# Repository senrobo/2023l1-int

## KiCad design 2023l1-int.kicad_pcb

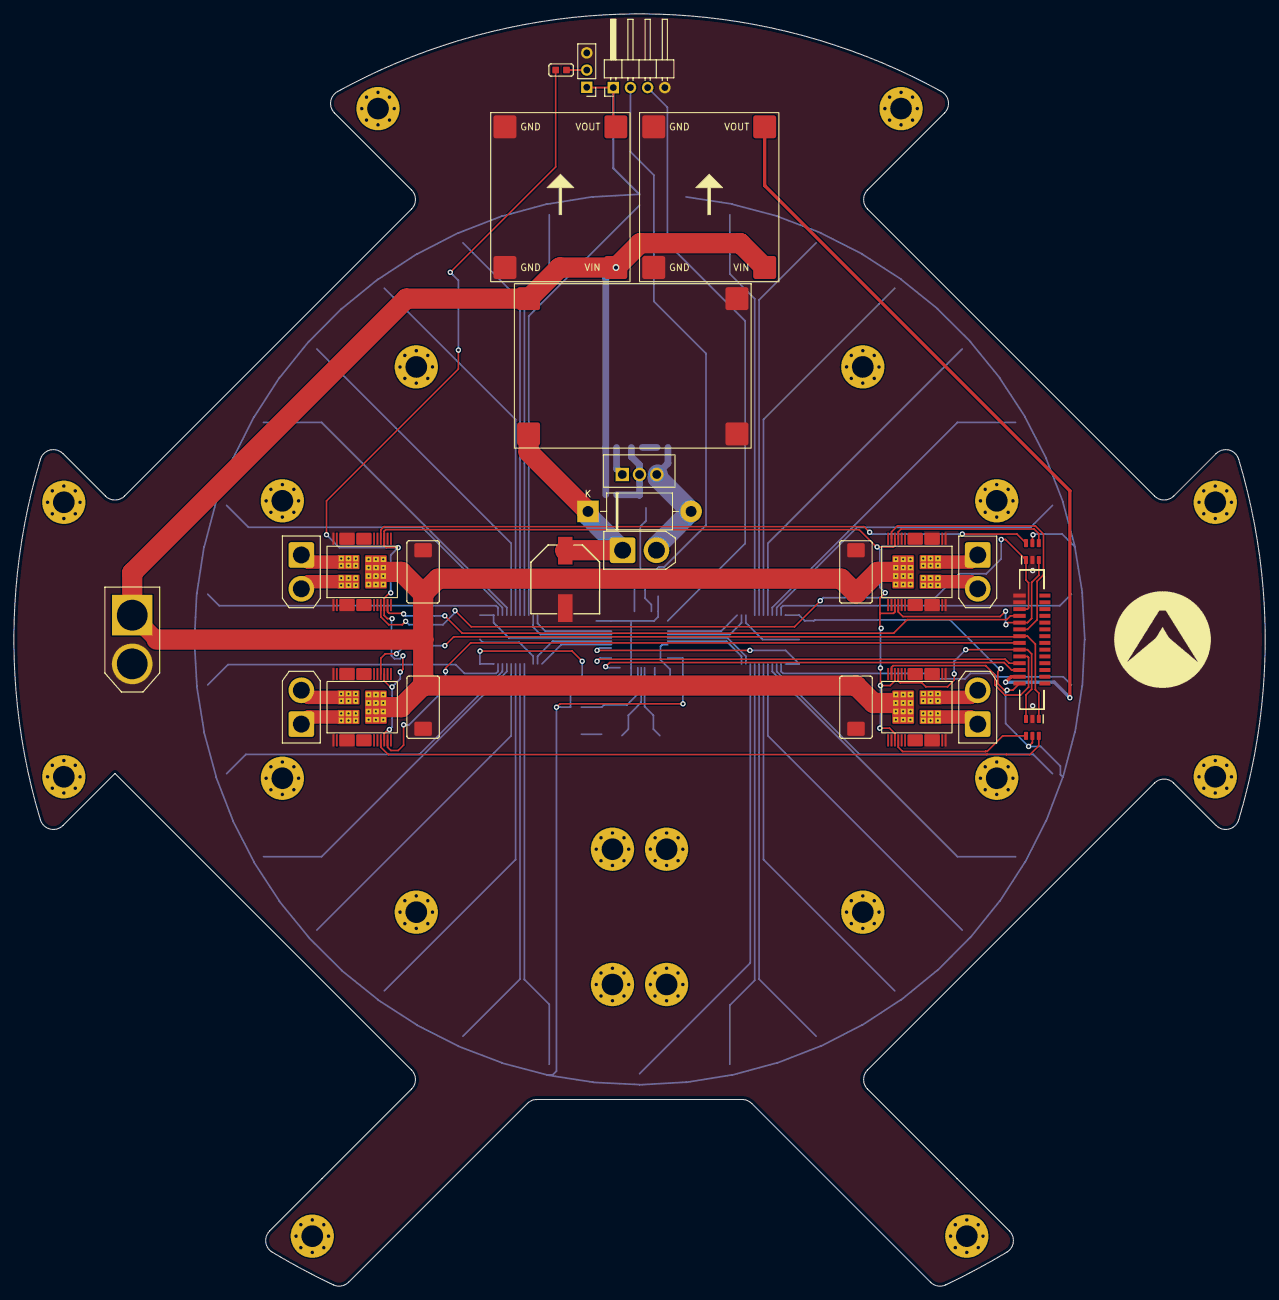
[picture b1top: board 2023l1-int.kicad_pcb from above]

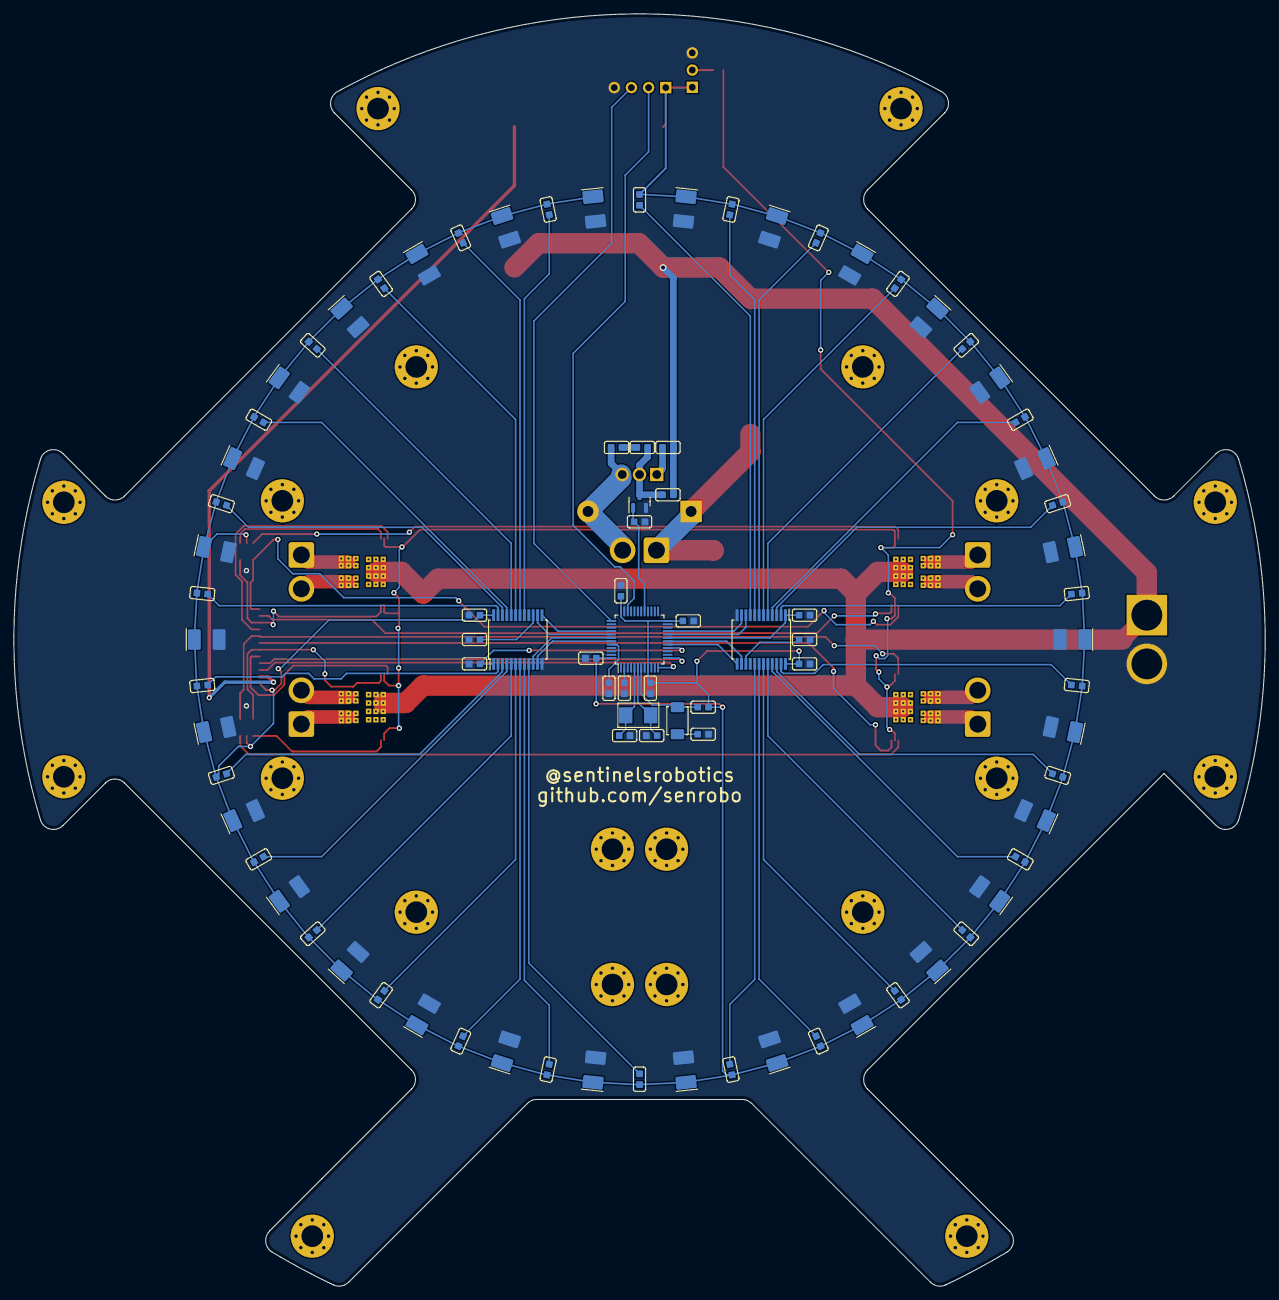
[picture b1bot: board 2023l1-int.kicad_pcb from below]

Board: 2 copper layers, 185.0 x 188.1 mm, 133 parts (87 on the bottom side), 84 nets.

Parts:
Boost1: boost
C4, C5: 22p; cap0603
C6, C12, C13, C14, C15, C20: 0.1u; cap0603
C7: 1500pF; cap0603
C11: 1000u; CAPAE1030X1270N
C16, C17, C18, C19: 220u; EIA-7343-D
D2: 1N5401; D_DO-201AD_P15.24mm_Horizontal
D3: LED; led0603
D5, D6, D7, D8, D9, D10, D11, D12, D13, D14, D15, D16, D17, D18, D19, D20, D21, D22, D23, D24, D25, D26, D27, D28, D29, D30, D31, D32, D33, D34: LED; LED-3528
H1, H2, H3, H4, H5, H6, H7, H8, H9, H10, H11, H12, H13, H14, H15, H16, H17, H18, H19, H20: MountingHole_Pad; MountingHole_3.2mm_M3_Pad_Via
IC1: STM32F103CBTx; LQFP-48_7x7mm_P0.5mm
IC2, IC3: SN74LVC2G04DBVTG4; SOT95P280X145-6N
J1: 52610-1433; 526101433
J2: XT30; AMASS_XT30-F
J3: PGMR; PinHeader_1x04_P2.54mm_Horizontal
J4: FL; AMASS_XT30-F
J5: FR; AMASS_XT30-F
J6: BL; AMASS_XT30-F
J7: BR; AMASS_XT30-F
J8: XT60; AMASS_XT60-M
Q1: STP75NF75; TO255P1040X460X2890-3
Q2: AO3400A; SOT-23
R1, R2, R3, R4, R5, R6, R7, R8, R9, R10, R11, R12, R13, R14, R15, R16, R17, R18, R19, R20, R21, R22, R23, R24, R25, R26, R27, R28, R29, R30: R_Photo; ALS-PT19
R31, R33, R38, R39, R43, R44, R45: 10K; res0603
R35: 20; res0603
R36, R41: 1K; res0603
R37, R42: 3K24; res0603
SW1: STM RST; SW_PUSH_SPST
SW3: M SW; PinHeader_1x03_P2.54mm_Vertical
U1, U3: buck
U2, U4: CD74HC4067SM; SSOP-24_5.3x8.2mm_P0.65mm
U5, U6, U7, U8: VNH5050A-E; SOP50P1030X247-39N
Y1: 8Mhz; Crystal

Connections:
+3V3: C6.2, C12.1, C13.1, C14.1, C15.1, C20.2, D5.2 (A), D6.2 (A), D7.2 (A), D8.2 (A), D9.2 (A), D10.2 (A), D11.2 (A), D12.2 (A), D13.2 (A), D14.2 (A), D15.2 (A), D16.2 (A), D17.2 (A), D18.2 (A), D19.2 (A), D20.2 (A), D21.2 (A), D22.2 (A), D23.2 (A), D24.2 (A), D25.2 (A), D26.2 (A), D27.2 (A), D28.2 (A), D29.2 (A), D30.2 (A), D31.2 (A), D32.2 (A), D33.2 (A), D34.2 (A), IC1.9 (VDDA), IC1.24 (VDD), IC1.36 (VDD), IC1.48 (VDD), IC2.5 (VCC), IC3.5 (VCC), J1.1, J3.1, R1.1, R2.1, R3.1, R4.1, R5.1, R6.1, R7.1, R8.1, R9.1, R10.1, R11.1, R12.1, R13.1, R14.1, R15.1, R16.1, R17.1, R18.1, R19.1, R20.1, R21.1, R22.1, R23.1, R24.1, R25.1, R26.1, R27.1, R28.1, R29.1, R30.1, R45.1, SW3.1 (A), U1.VOUT, U2.24 (VCC), U4.24 (VCC)
+5V: J1.3, U3.VOUT
+12V: Boost1.1 (VIN), C16.1, C17.1, C18.1, C19.1, J8.2 (POS), R36.1, R39.1, U1.VIN, U3.VIN, U5.39 (VCC), U6.39 (VCC), U7.39 (VCC), U8.39 (VCC)
+48V: Boost1.2 (VOUT), C11.1, D2.1 (K), J2.2 (POS)
/!BL DIR: IC3.4 (2Y), U7.15 (INA)
/!BR DIR: IC3.6 (1Y), U8.22 (INB)
/!FL DIR: IC2.4 (2Y), U5.22 (INB)
/!FR DIR: IC2.6 (1Y), U6.15 (INA)
/BL A: J6.2 (POS), U7.38 (OUTA)
/BL B: J6.1 (NEG), U7.37 (OUTB)
/BL DIR: IC3.3 (2A), J1.19, U7.22 (INB)
/BL PWM: J1.17, U7.17 (IN_PWM)
/BOOT: IC1.44 (BOOT0), R33.2
/BR A: J7.1 (NEG), U8.38 (OUTA)
/BR B: J7.2 (POS), U8.37 (OUTB)
/BR DIR: IC3.1 (1A), J1.23, U8.15 (INA)
/BR PWM: J1.21, U8.17 (IN_PWM)
/FL A: J4.1 (NEG), U5.38 (OUTA)
/FL B: J4.2 (POS), U5.37 (OUTB)
/FL DIR: IC2.3 (2A), J1.11, U5.15 (INA)
/FL PWM: J1.9, U5.17 (IN_PWM)
/FR A: J5.2 (POS), U6.38 (OUTA)
/FR B: J5.1 (NEG), U6.37 (OUTB)
/FR DIR: IC2.1 (1A), J1.15, U6.22 (INB)
/FR PWM: J1.13, U6.17 (IN_PWM)
/M1: IC1.16 (PA6), R37.2, U2.1 (COM)
/M1 S0: IC1.42 (PB6), U2.10 (S0)
/M1 S1: IC1.43 (PB7), U2.11 (S1)
/M1 S2: IC1.41 (PB5), U2.14 (S2)
/M1 S3: IC1.40 (PB4), U2.13 (S3)
/M2: IC1.19 (PB1), R42.2, U4.1 (COM)
/M SW: R44.2, U5.16 (ENA), U5.21 (ENB), U6.16 (ENA), U6.21 (ENB), U7.16 (ENA), U7.21 (ENB), U8.16 (ENA), U8.21 (ENB)
/RST: IC1.7 (NRST), R45.2, SW1.2
/RX: IC1.13 (PA3), J1.7
/S0: IC1.20 (PB2), U4.10 (S0)
/S1: IC1.21 (PB10), U4.11 (S1)
/S2: IC1.18 (PB0), U4.14 (S2)
/S3: IC1.17 (PA7), U4.13 (S3)
/SWCLK: IC1.37 (PA14), J3.3
/SWDIO: IC1.34 (PA13), J3.2
/Sol: IC1.29 (PA8), Q2.1 (G), R31.1
/TX: IC1.12 (PA2), J1.5
GND: Boost1.3 (GND), Boost1.4 (GND), C4.2, C5.2, C6.1, C11.2, C12.2, C13.2, C14.2, C15.2, C16.2, C17.2, C18.2, C19.2, C20.1, D3.1 (K), D5.1 (K), D6.1 (K), D7.1 (K), D8.1 (K), D9.1 (K), D10.1 (K), D11.1 (K), D12.1 (K), D13.1 (K), D14.1 (K), D15.1 (K), D16.1 (K), D17.1 (K), D18.1 (K), D19.1 (K), D20.1 (K), D21.1 (K), D22.1 (K), D23.1 (K), D24.1 (K), D25.1 (K), D26.1 (K), D27.1 (K), D28.1 (K), D29.1 (K), D30.1 (K), D31.1 (K), D32.1 (K), D33.1 (K), D34.1 (K), IC1.8 (VSSA), IC1.23 (VSS), IC1.35 (VSS), IC1.47 (VSS), IC2.2 (GND), IC3.2 (GND), J1.25, J1.27, J3.4, J8.1 (NEG), Q2.2 (S), R31.2, R33.1, R37.1, R38.1, R41.2, R42.1, R43.1, SW3.3 (C), U1.GND, U2.12 (GND), U3.GND, U4.12 (GND), U5.GND, U6.GND, U7.GND, U8.GND
unnamed: C7.1, R35.2
unnamed: D2.2 (A), J2.1 (NEG), Q1.3, R35.1
unnamed: D3.2 (A), IC1.2 (PC13)
unnamed: C4.1, IC1.5 (PD0), Y1.2
unnamed: C5.1, IC1.6 (PD1), Y1.1
unnamed: Q1.1, R36.2
unnamed: C7.2, Q1.2, Q2.3 (D), R39.2
unnamed: R41.1, SW1.1
unnamed: R44.1, SW3.2 (B)
unnamed: R1.2, U2.9 (I0)
unnamed: R2.2, U2.8 (I1)
unnamed: R3.2, U2.7 (I2)
unnamed: R4.2, U2.6 (I3)
unnamed: R5.2, U2.5 (I4)
unnamed: R6.2, U2.4 (I5)
unnamed: R7.2, U2.3 (I6)
unnamed: R8.2, U2.2 (I7)
unnamed: R9.2, U2.23 (I8)
unnamed: R10.2, U2.22 (I9)
unnamed: R11.2, U2.21 (I10)
unnamed: R12.2, U2.20 (I11)
unnamed: R13.2, U2.19 (I12)
unnamed: R14.2, U2.18 (I13)
unnamed: R15.2, U2.17 (I14)
unnamed: R38.2, U2.15 (~E)
unnamed: R16.2, U4.9 (I0)
unnamed: R17.2, U4.8 (I1)
unnamed: R18.2, U4.7 (I2)
unnamed: R19.2, U4.6 (I3)
unnamed: R20.2, U4.5 (I4)
unnamed: R21.2, U4.4 (I5)
unnamed: R22.2, U4.3 (I6)
unnamed: R23.2, U4.2 (I7)
unnamed: R24.2, U4.23 (I8)
unnamed: R25.2, U4.22 (I9)
unnamed: R26.2, U4.21 (I10)
unnamed: R27.2, U4.20 (I11)
unnamed: R28.2, U4.19 (I12)
unnamed: R29.2, U4.18 (I13)
unnamed: R30.2, U4.17 (I14)
unnamed: R43.2, U4.15 (~E)

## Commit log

2023-05-12 init push
2023-05-12 idl kicad
2023-05-18 kill me
2023-05-18 I HATE DOING L1
2023-05-21 left with boost
2023-05-22 done component placement
2023-05-22 inital wiring
2023-05-22 mux wiring done
2023-05-22 stm32 wiring done
2023-05-22 time to do it again
2023-05-22 transitioning
2023-05-22 fl and fr done
2023-05-23 left with msw
2023-05-23 done
2023-05-23 jlcpcb
2023-05-23 step
2023-05-23 decal
